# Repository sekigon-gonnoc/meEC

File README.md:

# meEC

| | |
|-|-|
|NIZスイッチLEDなし|NIZスイッチLEDあり|
|||
| | |
|BTOスイッチLEDなし|BTOスイッチLEDあり|

- [部品リスト](#部品リスト)
  - [キットに同梱されている部品](#キットに同梱されている部品)
  - [キット以外に必要な部品](#キット以外に必要な部品)
- [組み立て手順](#組み立て手順)
  - [EC microにType-Cコネクタをはんだ付けする](#ec-microにtype-cコネクタをはんだ付けする)
  - [(メイン基板にLEDをはんだ付けする)](#メイン基板にledをはんだ付けする)
  - [メイン基板にリセットスイッチをはんだ付けする](#メイン基板にリセットスイッチをはんだ付けする)
  - [メイン基板にEC microを取り付ける](#メイン基板にec-microを取り付ける)
  - [トッププレートにスペーサーをネジ止めする](#トッププレートにスペーサーをネジ止めする)
  - [トッププレートにスイッチを取り付ける](#トッププレートにスイッチを取り付ける)
  - [トッププレートとメイン基板をネジ止めする](#トッププレートとメイン基板をネジ止めする)
- [ファームウェア](#ファームウェア)

## 部品リスト
### キットに同梱されている部品
|部品|数|
|-|-|
|EC micro|1|
|USB Type-C コネクタ|1|
|メイン基板|1|
|トッププレート|1|
|タクトスイッチ|1|
|M2ネジ|8|
|M2x5スペーサー|4|
|ゴム足|4|

### キット以外に必要な部品

|部品|数|入手先|
|-|-|-|
|12ピンコンスルーまたはピンヘッダ|2|遊舎工房など|
||||
|**BTOスイッチ用**|
|ADELCPS 静電容量スイッチ4点セット|4キー分|https://yushakobo.jp/shop/a0500es-01-1/, https://btoshop.jp/2020/09/25/adelcps/mp
|ラバードーム|必要分|https://yushakobo.jp/shop/a0500er-01-1/, https://btoshop.jp/2020/09/25/adelcpru/|
||||
|**NIZ ECスイッチ用**|
|NIZ EC Switch |4|https://www.nizkeyboard.com/collections/ornaments/products/2019-new-niz-ec-switch|
|ラバードーム|必要分|https://www.nizkeyboard.com/collections/ornaments/products/ec-silicone-domes-35g-45g-55g, 上記ラバードームも可|
|コニックリング|4|NIZ用のバラ売りはないのでBTOのセットなどから流用する|
||||
|**LED対応版オプション**|||
|YS-SK6812MINI-E|4|遊舎工房など|

## 組み立て手順
### EC microにType-Cコネクタをはんだ付けする
- 出荷時に貼り付けてあるカプトンテープは剥がさないほうが他の部品とブリッジしづらい

### (メイン基板にLEDをはんだ付けする)
- 行によってLEDの向きが違うので注意
  - シルクに`/`マークがついている方にLEDの切り欠きを合わせる

### メイン基板にリセットスイッチをはんだ付けする
### メイン基板にEC microを取り付ける
- コンスルーを使う場合、EC micro側もメイン基板側もはんだ付けは不要
- コンスルーはスイッチ側に寄せる

### トッププレートにスペーサーをネジ止めする
### トッププレートにスイッチを取り付ける
- BTOのスイッチの場合は切り欠きが横向きになるように嵌めて、ラバーシートの切り欠きにスイッチの突起を通す
- ステムの向きに注意

### トッププレートとメイン基板をネジ止めする
- トッププレートの穴にコンスルーが通っている（コンスルーを押しつぶしていない）ことを確認

## ファームウェア
- リポジトリを取得
  - https://github.com/sekigon-gonnoc/qmk_firmware/tree/dev/sekigon
- atmel-dfu経由で書き込み
  - リセットすると自動でブートローダが起動する
  ```
  make meec:dfu
  ```

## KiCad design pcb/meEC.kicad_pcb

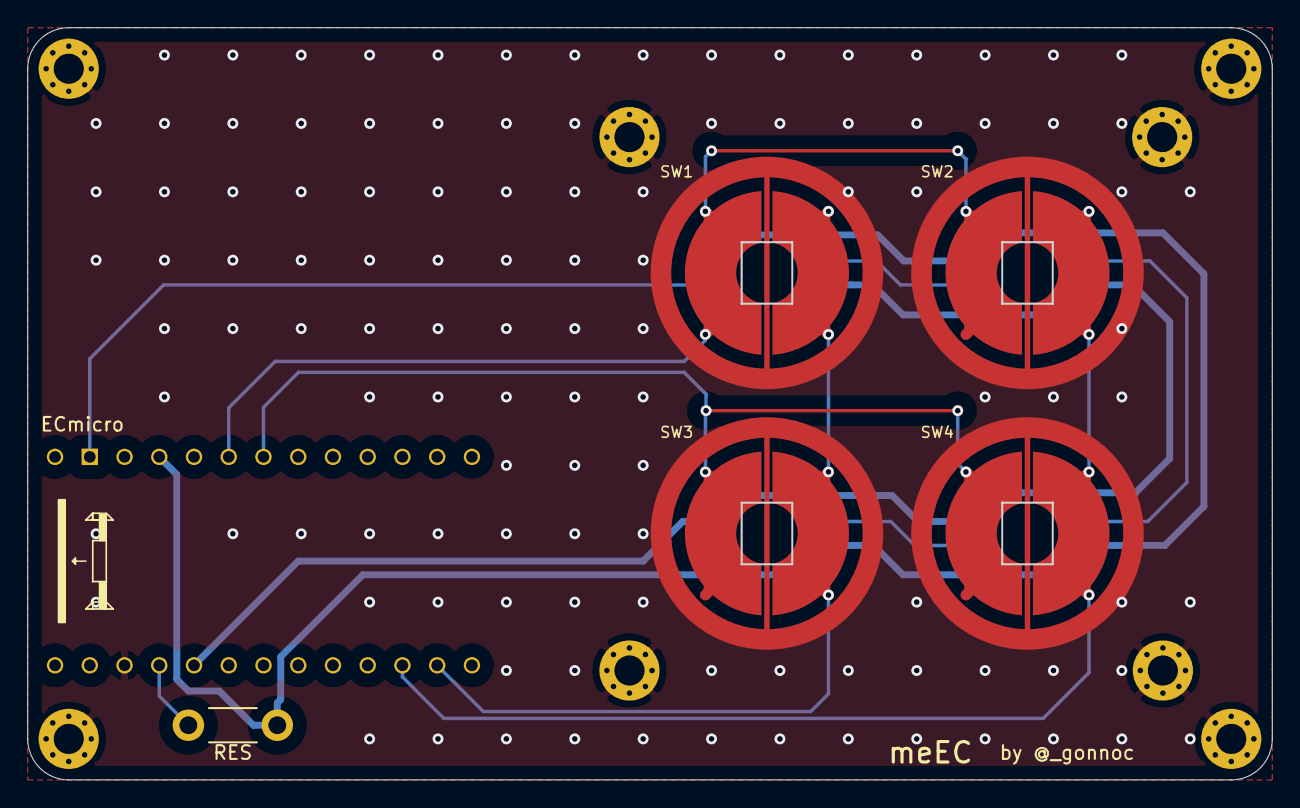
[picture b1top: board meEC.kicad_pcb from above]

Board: 2 copper layers, 90.9 x 54.9 mm, 18 parts (1 on the bottom side), 12 nets.

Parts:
D1, D2, D3, D4: WS2812B; YS-SK6812MINI_rev
H1, H2, H3, H4, H5, H6, H7, H8: M2; MountingHole_2.2mm_M2_Pad_Via
SW1, SW2, SW3, SW4: EC_SW; ec_pad_led2
SW5: SW_Push; TactSW_2Pin
U1: ECmicro; BLEMicroPro

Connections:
C0: SW1.2, SW3.2, U1.15
C1: SW2.2, SW4.2, U1.16
GND: D1.3, D2.3, D3.3, D4.3, SW5.2, U1.4
GNDA: H1.1, H2.1, H3.1, H4.1, H5.1, H6.1, H7.1, H8.1, SW1.3, SW2.3, SW3.3, SW4.3, U1.24
LED: D1.4, U1.2
unnamed: D1.2, D2.4
unnamed: D2.2, D3.4
unnamed: D3.2, D4.4
unnamed: SW5.1, U1.23
R0: SW1.1, SW2.1, U1.6
R1: SW3.1, SW4.1, U1.7
VCC: D1.1, D2.1, D3.1, D4.1, U1.22

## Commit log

2020-10-02 Create LICENSE
2020-10-02 Add KiCad files
